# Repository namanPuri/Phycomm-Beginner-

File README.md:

# Phycomm-Beginner-
Contains all stuff for beginner board

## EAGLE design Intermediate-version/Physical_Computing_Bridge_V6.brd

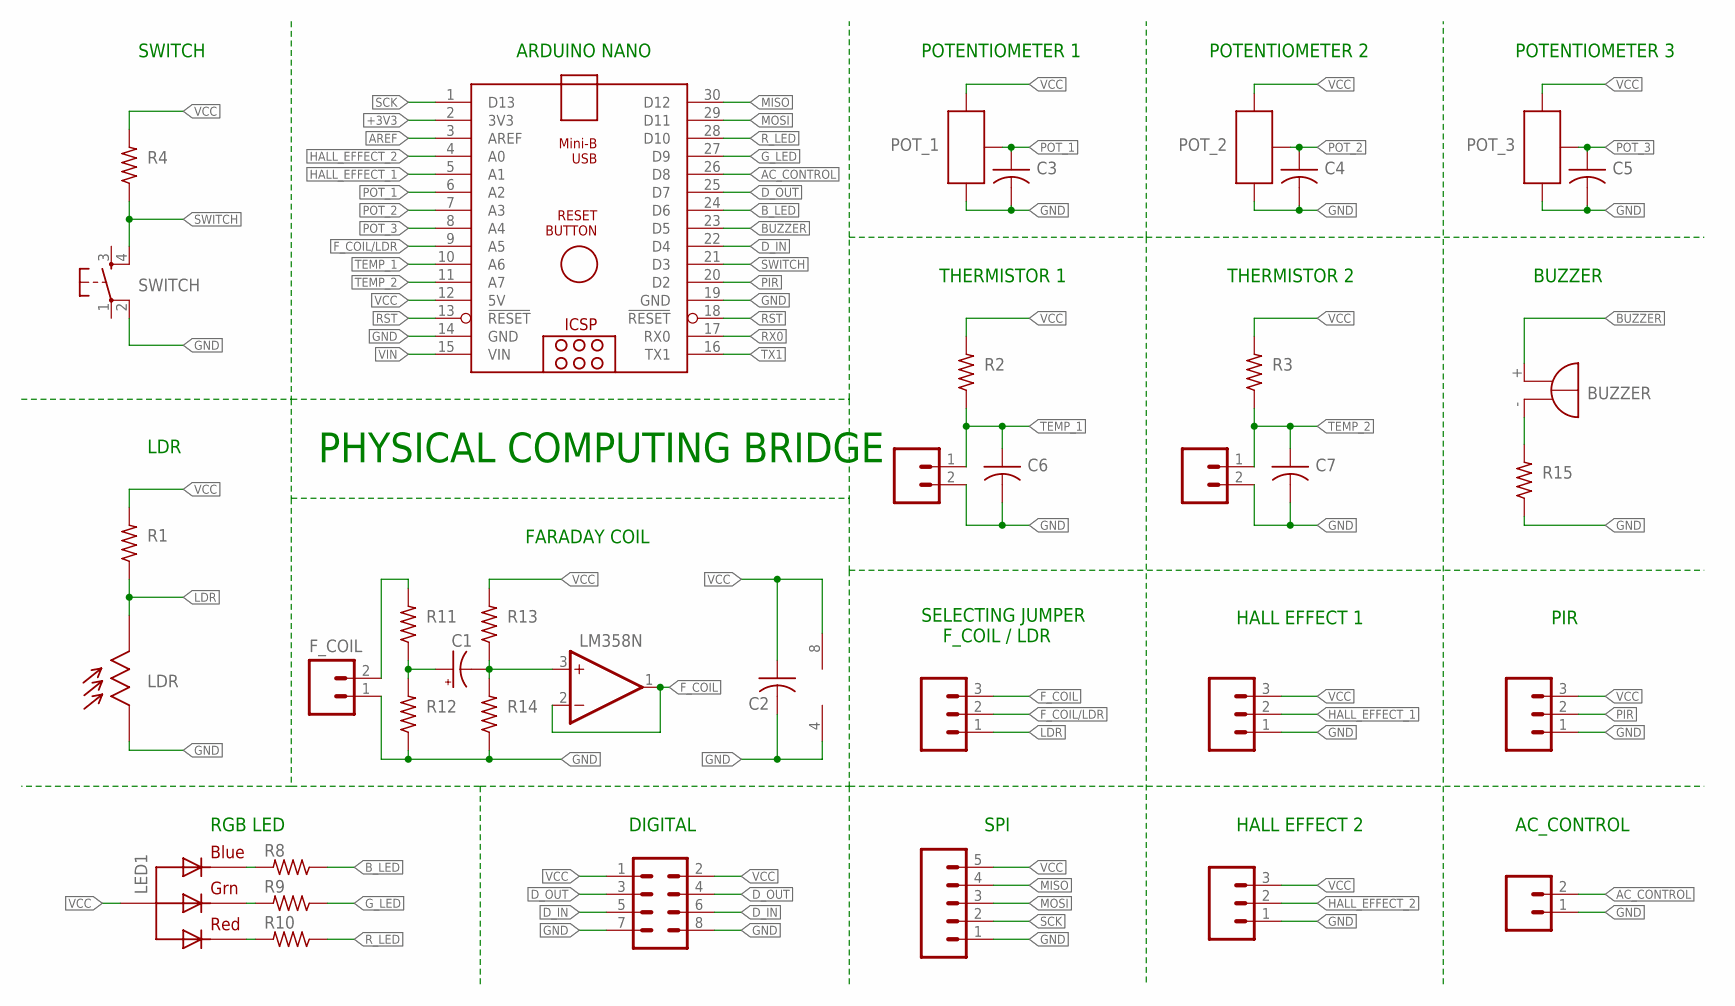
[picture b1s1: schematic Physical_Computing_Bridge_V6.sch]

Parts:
AC_CONTROL: CONN_02POLAR; MOLEX-1X2
ARDUINO_NANO1: ARDUINO_NANO
BUZZER: BUZZER; F/TMB
C1: CPOL-USE2.5-7; E2,5-7
C2, C3, C4, C5, C6, C7: C-US025-025X050; C025-025X050
DIGITAL: CONN_04X2; 2X4
F_COIL: CONN_02POLAR; MOLEX-1X2
HALL_EFFECT_1, HALL_EFFECT_2: CONN_03POLAR; MOLEX-1X3
IC1: LM358N; DIL08
LDR: CDSLDR3MM; LDR3MM
LED1: RGBLED_CA-5MM; LED5MMRGB
PIR: CONN_03POLAR; MOLEX-1X3
POT_1, POT_2, POT_3: POTNORMAL; RJ9W
R1, R2, R3, R4, R8, R9, R10, R11, R12, R13, R14, R15: R-US_0204/7; 0204/7
SELECTINGJUMPER: CONN_03LONGPADS; 1X03_LONGPADS
SPI: CONN_05PTH_LONGPADS; 1X05_LONGPADS
SWITCH: OMRON_SWITCH_40-XX; B3F-40XX
THERMISTOR1, THERMISTOR2: CONN_02POLAR; MOLEX-1X2

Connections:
+3V3: ARDUINO_NANO1.2 (3V3)
AC_CONTROL: AC_CONTROL.2, ARDUINO_NANO1.26 (D8)
AREF: ARDUINO_NANO1.3 (AREF)
BUZZER: ARDUINO_NANO1.23 (D5), BUZZER.+
B_LED: ARDUINO_NANO1.24 (D6), R8.1
D_IN: ARDUINO_NANO1.22 (D4), DIGITAL.5, DIGITAL.6
D_OUT: ARDUINO_NANO1.25 (D7), DIGITAL.3, DIGITAL.4
F_COIL: IC1.1 (OUT), IC1.2 (-IN), SELECTINGJUMPER.3
F_COIL/LDR: ARDUINO_NANO1.9 (A5), SELECTINGJUMPER.2
GND: AC_CONTROL.1, ARDUINO_NANO1.14 (GND), ARDUINO_NANO1.19 (GND), C2.2, C3.2, C4.2, C5.2, C6.2, C7.2, DIGITAL.7, DIGITAL.8, F_COIL.1, HALL_EFFECT_1.1, HALL_EFFECT_2.1, IC1.4 (V-), LDR.P$1, PIR.1, POT_1.E, POT_2.E, POT_3.E, R12.1, R14.1, R15.1, SPI.1, SWITCH.2 (P1), THERMISTOR1.2, THERMISTOR2.2
G_LED: ARDUINO_NANO1.27 (D9), R9.1
HALL_EFFECT_1: ARDUINO_NANO1.5 (A1), HALL_EFFECT_1.2
HALL_EFFECT_2: ARDUINO_NANO1.4 (A0), HALL_EFFECT_2.2
LDR: LDR.P$2, R1.1, SELECTINGJUMPER.1
MISO: ARDUINO_NANO1.30 (D12), SPI.4
MOSI: ARDUINO_NANO1.29 (D11), SPI.3
unnamed: LED1.1 (RED), R10.2
unnamed: LED1.3 (GREEN), R9.2
unnamed: LED1.4 (BLUE), R8.2
unnamed: F_COIL.2, R11.2
unnamed: C1.+, R11.1, R12.2
unnamed: C1.-, IC1.3 (+IN), R13.1, R14.2
unnamed: BUZZER.-, R15.2
PIR: ARDUINO_NANO1.20 (D2), PIR.2
POT_1: ARDUINO_NANO1.6 (A2), C3.1, POT_1.S
POT_2: ARDUINO_NANO1.7 (A3), C4.1, POT_2.S
POT_3: ARDUINO_NANO1.8 (A4), C5.1, POT_3.S
RST: ARDUINO_NANO1.13 (!RESET), ARDUINO_NANO1.18 (!RESET)
RX0: ARDUINO_NANO1.17 (RX0)
R_LED: ARDUINO_NANO1.28 (D10), R10.1
SCK: ARDUINO_NANO1.1 (D13), SPI.2
SWITCH: ARDUINO_NANO1.21 (D3), R4.1, SWITCH.4 (S1)
TEMP_1: ARDUINO_NANO1.10 (A6), C6.1, R2.1, THERMISTOR1.1
TEMP_2: ARDUINO_NANO1.11 (A7), C7.1, R3.1, THERMISTOR2.1
TX1: ARDUINO_NANO1.16 (TX1)
VCC: ARDUINO_NANO1.12 (5V), C2.1, DIGITAL.1, DIGITAL.2, HALL_EFFECT_1.3, HALL_EFFECT_2.3, IC1.8 (V+), LED1.2 (VCC), PIR.3, POT_1.A, POT_2.A, POT_3.A, R1.2, R2.2, R3.2, R4.2, R13.2, SPI.5
VIN: ARDUINO_NANO1.15 (VIN)

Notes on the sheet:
PHYSICAL COMPUTING BRIDGE
ARDUINO NANO
SWITCH
LDR
FARADAY COIL
RGB LED
DIGITAL
SPI
SELECTING JUMPER F_COIL / LDR
HALL EFFECT 1
HALL EFFECT 2
PIR
AC_CONTROL
BUZZER
THERMISTOR 2
THERMISTOR 1
POTENTIOMETER 1
POTENTIOMETER 2
POTENTIOMETER 3

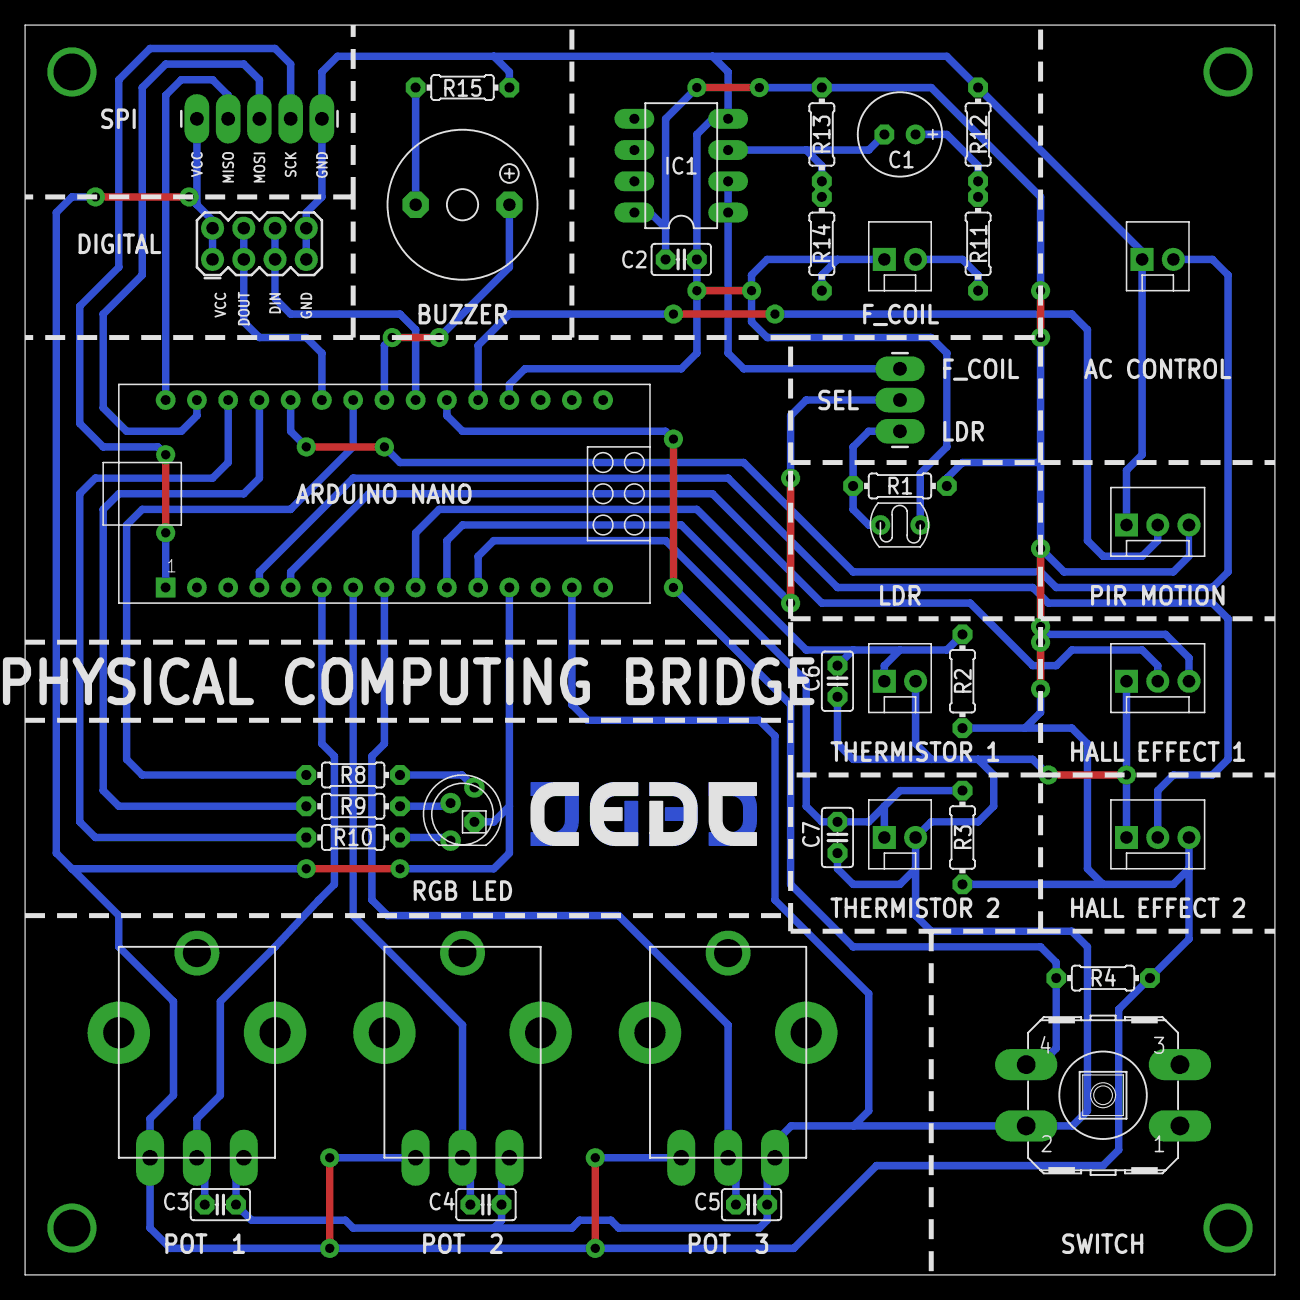
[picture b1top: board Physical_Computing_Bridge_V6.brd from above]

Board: 2 copper layers, 101.6 x 101.6 mm, 40 parts (0 on the bottom side), 32 nets.

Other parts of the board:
U$2: LOGO-CEDT-BOT-18MM
U$3: LOGO-CEDT-SILK-18MM

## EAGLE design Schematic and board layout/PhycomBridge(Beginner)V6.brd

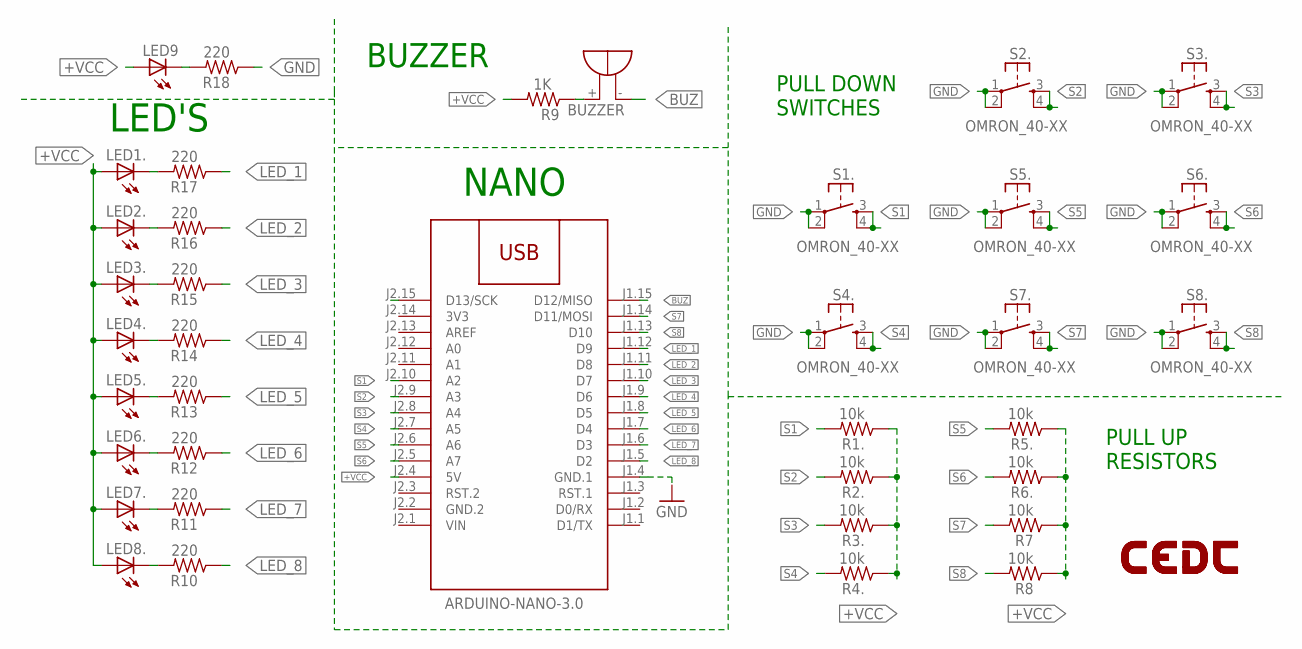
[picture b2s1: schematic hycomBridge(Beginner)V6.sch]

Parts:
ARDUINO_NANO: ARDUINO-NANO-3.0
LED1., LED2., LED3., LED4., LED5., LED6., LED7., LED8.: LED5MM
LED9: LED3MM
LOGO1: LOGO-CEDTBOT-18MM; LOGO-CEDT-BOT-18MM
LOGO2: LOGO-CEDTSILK-18MM; LOGO-CEDT-SILK-18MM
R1., R2., R3., R4., R5., R6., R7, R8: 10k; 0207/10
R9: 1K; 0207/10
R10, R11, R12, R13, R14, R15, R16, R17, R18: 220; 0207/10
S1., S2., S3., S4., S5., S6., S7., S8.: OMRON_40-XX; B3F-40XX
SG1: BUZZER; F/TMB

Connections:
3V3: ARDUINO_NANO.J2.14 (3V3)
+VCC: ARDUINO_NANO.J2.4 (5V), LED1..A, LED2..A, LED3..A, LED4..A, LED5..A, LED6..A, LED7..A, LED8..A, LED9.A, R1..1, R2..1, R3..1, R4..1, R5..1, R6..1, R7.1, R8.1, R9.2
.: R9.1, SG1.+
BUZ: ARDUINO_NANO.J1.15 (D12/MISO), SG1.-
GND: ARDUINO_NANO.J1.4 (GND.1), R18.1, S1..1, S1..2 (P1), S2..1, S2..2 (P1), S3..1, S3..2 (P1), S4..1, S4..2 (P1), S5..1, S5..2 (P1), S6..1, S6..2 (P1), S7..1, S7..2 (P1), S8..1, S8..2 (P1)
GND.2: ARDUINO_NANO.J2.2 (GND.2)
LED_1: ARDUINO_NANO.J1.12 (D9), R17.1
LED_2: ARDUINO_NANO.J1.11 (D8), R16.1
LED_3: ARDUINO_NANO.J1.10 (D7), R15.1
LED_4: ARDUINO_NANO.J1.9 (D6), R14.1
LED_5: ARDUINO_NANO.J1.8 (D5), R13.1
LED_6: ARDUINO_NANO.J1.7 (D4), R12.1
LED_7: ARDUINO_NANO.J1.6 (D3), R11.1
LED_8: ARDUINO_NANO.J1.5 (D2), R10.1
unnamed: LED7..K (C), R11.2
unnamed: LED6..K (C), R12.2
unnamed: LED2..K (C), R16.2
unnamed: LED1..K (C), R17.2
unnamed: LED5..K (C), R13.2
unnamed: LED4..K (C), R14.2
unnamed: LED8..K (C), R10.2
unnamed: LED3..K (C), R15.2
unnamed: LED9.K (C), R18.2
S1: ARDUINO_NANO.J2.10 (A2), R1..2, S1..3 (S), S1..4 (S1)
S2: ARDUINO_NANO.J2.9 (A3), R2..2, S2..3 (S), S2..4 (S1)
S3: ARDUINO_NANO.J2.8 (A4), R3..2, S3..3 (S), S3..4 (S1)
S4: ARDUINO_NANO.J2.7 (A5), R4..2, S4..3 (S), S4..4 (S1)
S5: ARDUINO_NANO.J2.6 (A6), R5..2, S5..3 (S), S5..4 (S1)
S6: ARDUINO_NANO.J2.5 (A7), R6..2, S6..3 (S), S6..4 (S1)
S7: ARDUINO_NANO.J1.14 (D11/MOSI), R7.2, S7..3 (S), S7..4 (S1)
S8: ARDUINO_NANO.J1.13 (D10), R8.2, S8..3 (S), S8..4 (S1)
VIN: ARDUINO_NANO.J2.1 (VIN)

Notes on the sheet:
LED'S
NANO
PULL UP RESISTORS
PULL DOWN SWITCHES
BUZZER

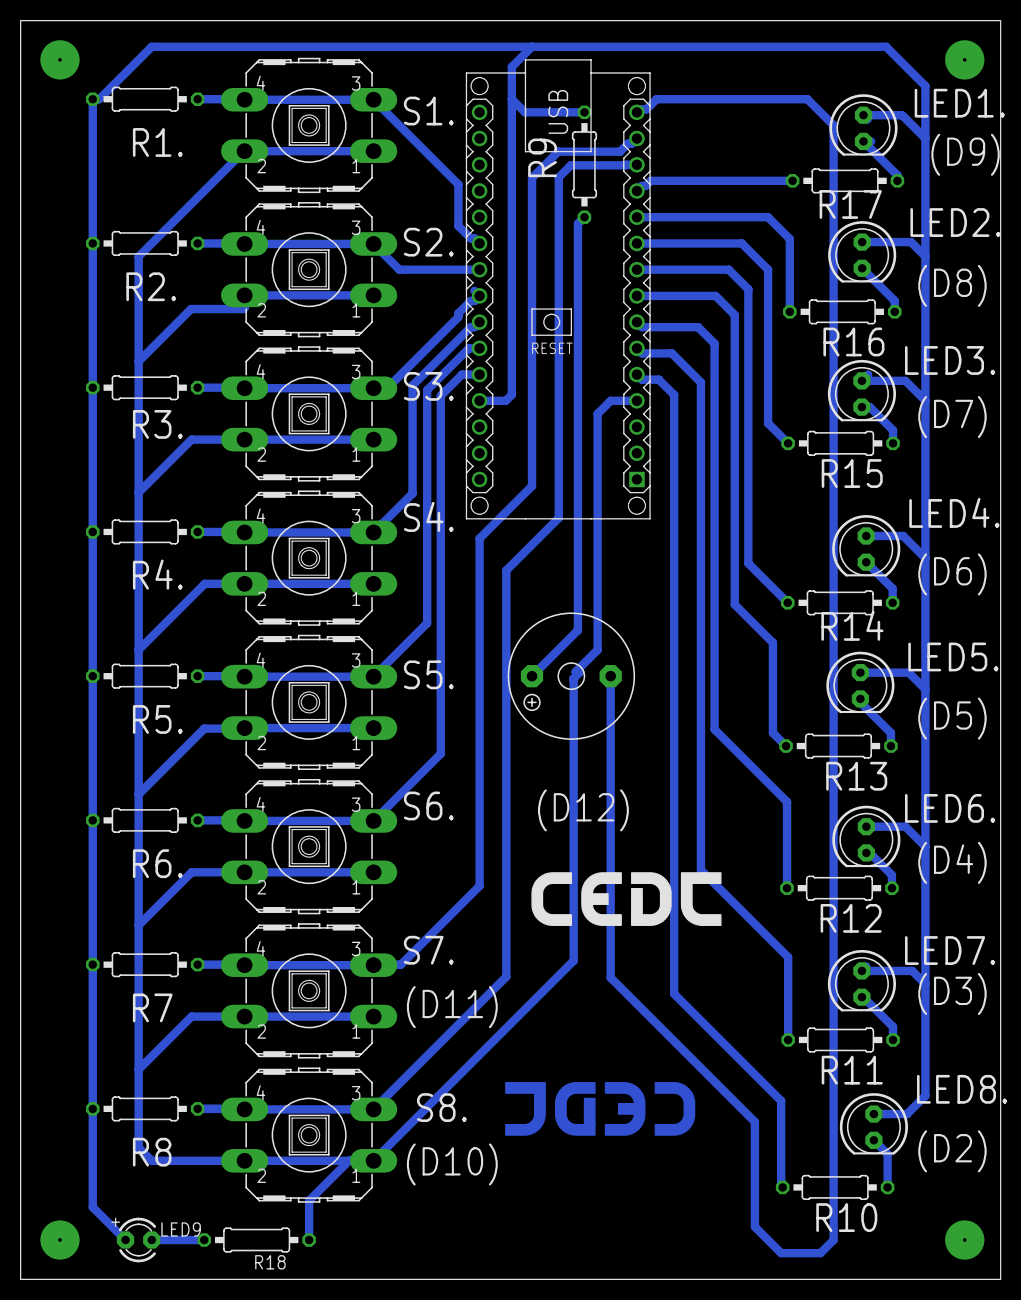
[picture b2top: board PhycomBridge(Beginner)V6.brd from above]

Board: 2 copper layers, 94.9 x 121.9 mm, 39 parts (0 on the bottom side), 29 nets.

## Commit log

2020-04-28 Rename PhycomBridge(Beginner)V6.brd to Schematic and board layout/PhycomBridge(Beginner)V6.brd
2020-04-28 Rename PhycomBridge(Beginner)V6.sch to Schematic and board layout/PhycomBridge(Beginner)V6.sch
2020-05-29 Create Beginner-version
2020-05-29 Rename Schematic and board layout/PhycomBridge(Beginner)V6.brd to Beginner-version/Schematic and board layoutPhycomBridge(Beginner)V6.brd
2020-05-29 Rename Schematic and board layoutPhycomBridge(Beginner)V6.brd to PhycomBridge(Beginner)V6.brd
2020-05-29 Rename Schematic and board layout/PhycomBridge(Beginner)V6.sch to Beginner-version/hycomBridge(Beginner)V6.sch
2020-05-29 Rename hycomBridge(Beginner)V6.sch to PhycomBridge(Beginner)V6.sch
2020-06-03 Add beginner projects
2020-06-03 Add intermediate projects
2020-06-03 Modified plotting interface for Jupyter Notebooks
    Basically modified the phySyncFirmata plotting interface (common_Utility) to common_Utility_2 such that the Matplotlib funcAnimation commands are written in the working Jupyter Notebook instead of th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
    This file should be pasted in the phySyncFirmata/phyCom directory so that it can be imported. If using virtual environment, the exact path will be (environment_name)/lib/python3.6/site-packages/phySy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

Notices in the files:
parts and their libraries:
diy-modules: Released under the Creative Commons Attribution 4.0 International License: http://creativecommons.org/licenses/by/4.0
SparkFun-Connectors: Licensing: Creative Commons ShareAlike 4.0 International - https://creativecommons.org/licenses/by-sa/4.0
